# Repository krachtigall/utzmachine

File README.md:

# UTZmachine
A multi-user MIDI-controller and sampler.

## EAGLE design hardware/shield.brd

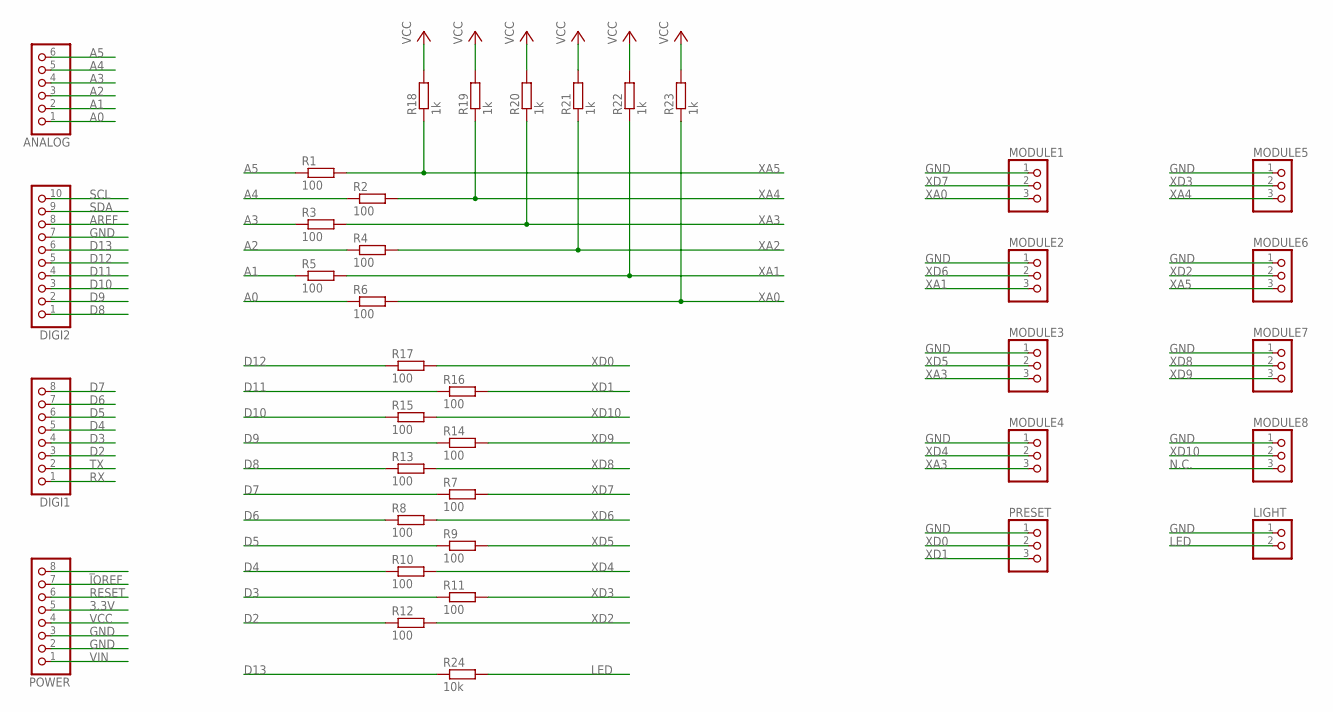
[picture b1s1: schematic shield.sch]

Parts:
ANALOG: PINHD-1X6; 1X06
DIGI1: PINHD-1X8; 1X08
DIGI2: PINHD-1X10; 1X10
LIGHT: PINHD-1X2; 1X02
MODULE1, MODULE2, MODULE3, MODULE4, MODULE5, MODULE6, MODULE7, MODULE8: PINHD-1X3; 1X03
POWER: PINHD-1X8; 1X08
PRESET: PINHD-1X3; 1X03
R1, R2, R3, R4, R5, R6, R7, R8, R9, R10, R11, R12, R13, R14, R15, R16, R17: 100; 0207/7
R18, R19, R20, R21, R22, R23: 1k; 0207/7
R24: 10k; 0207/7

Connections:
3.3V: POWER.5
A0: ANALOG.1, R6.1
A1: ANALOG.2, R5.1
A2: ANALOG.3, R4.1
A3: ANALOG.4, R3.1
A4: ANALOG.5, R2.1
A5: ANALOG.6, R1.1
AREF: DIGI2.8
D2: DIGI1.3, R12.1
D3: DIGI1.4, R11.1
D4: DIGI1.5, R10.1
D5: DIGI1.6, R9.1
D6: DIGI1.7, R8.1
D7: DIGI1.8, R7.1
D8: DIGI2.1, R13.1
D9: DIGI2.2, R14.1
D10: DIGI2.3, R15.1
D11: DIGI2.4, R16.1
D12: DIGI2.5, R17.1
D13: DIGI2.6, R24.1
GND: DIGI2.7, LIGHT.1, MODULE1.1, MODULE2.1, MODULE3.1, MODULE4.1, MODULE5.1, MODULE6.1, MODULE7.1, MODULE8.1, POWER.2, POWER.3, PRESET.1
IOREF: POWER.7
LED: LIGHT.2, R24.2
N.C.: MODULE8.3
RESET: POWER.6
RX: DIGI1.1
SCL: DIGI2.10
SDA: DIGI2.9
TX: DIGI1.2
VCC: POWER.4, R18.2, R19.2, R20.2, R21.2, R22.2, R23.2
VIN: POWER.1
XA0: MODULE1.3, R6.2, R23.1
XA1: MODULE2.3, R5.2, R22.1
XA2: R4.2, R21.1
XA3: MODULE3.3, MODULE4.3, R3.2, R20.1
XA4: MODULE5.3, R2.2, R19.1
XA5: MODULE6.3, R1.2, R18.1
XD0: PRESET.2, R17.2
XD1: PRESET.3, R16.2
XD2: MODULE6.2, R12.2
XD3: MODULE5.2, R11.2
XD4: MODULE4.2, R10.2
XD5: MODULE3.2, R9.2
XD6: MODULE2.2, R8.2
XD7: MODULE1.2, R7.2
XD8: MODULE7.2, R13.2
XD9: MODULE7.3, R14.2
XD10: MODULE8.2, R15.2
_: POWER.8

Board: 2 copper layers, 38 parts (0 on the bottom side), 38 nets, no tracks yet.

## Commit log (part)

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2014-08-24 Add sequencable harmonic oscillator
2014-08-25 added jimmmps matrixctrl
2014-08-25 add trigger-matrix to harmonic oscillator
2014-08-25 Removed matrix.pd as it was corrupt
2014-08-25 split gui_MetronomeBPM.pd to gui_metroBPM.pd & gui_metroClick.pd
2014-08-31 establish folder structure hierarchy
2014-08-31 gui elements get own folder
2014-08-31 add basic midi functions
2014-08-31 implement 4/8-track samplers with filedialog and preset saving
2014-08-31 clean up presets
2014-08-31 improve sampler gui and create single-channel mixer abstraction
2014-08-31 samplerX4: use just one bar for loading/saving samples
2014-08-31 increase size of sampler buttons
2014-08-31 remove filename dump from samplerX4
2014-09-01 change stopWatch behavior, rename gui-stopWatch to countDown and adapt modules that used those
2014-09-01 remove duplicate file stopWatchSec from utls
2014-09-01 implement tap metro with gui interface abstraction
2014-09-01 insert split object to prevent glitching metronome
2014-09-01 implement oneButtonTapMetro to loop kickdrum and by the way make the sampler midi-compatible
2014-09-02 autostart dsp on workspace
2014-10-04 add abstraction for mpkmini midi-input
2014-10-04 add record abstraction and guitar input abstraction for soundcard input
2014-10-04 add conversion abstraction ms -> bpm
2014-10-04 display peaks in mixer vu meters
2014-10-04 add preset choosing via midi pgmin
2014-10-04 remove dac~ from metroclick as outlet should be used
2014-10-04 create blue canvas for mixer
2014-10-04 midi-ctrlin -> volumes
2014-10-18 Make workspaceMPK ready for raspberry pi autostart
2014-10-18 create utz start script
2014-10-18 mv contents from workspaceMPK to utz
2014-10-18 create utz starters for pc and pi
2014-10-18 remove unused import from tapmetronome
2014-10-18 add multimelody composition as utz start theme
2014-10-18 dont output gui on top screen
2014-10-18 update starters for new utz name
2014-10-18 refactor mixer
2014-10-20 refactor sampler and add stop functionality to midi triggering
2014-10-20 implement mixer controller
2014-10-20 divide controls from audio processing in utz
2014-10-20 refine division
2014-10-20 remove gui from mixer
2014-10-20 add debug output for ctrlin and midiin
2014-10-20 remove usage of mpkmini
2014-10-20 remove mpkmini completely from patch
2014-10-20 remove controls subpatch
2014-10-20 use isolated mokdmini but dummy controls
2014-10-20 get original state without midisettings
2014-10-20 something wrong happened before...?
2014-10-20 initialize tapmetronome and increase shortest timedelta
2014-10-20 use ms instead of bpm to determine holdtime in tapmetro
2014-10-21 convert ms to sec in tapmetro
2014-10-21 add midi2multimelody starter
2014-10-21 include volume regulation
2014-10-21 fix volume bug: volume has to come before channel parameter
2014-10-21 initialize with program 0
2015-04-09 make it work for rpi2
2015-04-11 change samples
2015-04-11 change samples
    Former-commit-id: 6ad278d7dba5dec8e45f674af13e3b24edb2dd50
2015-04-11 change mixer preset
2015-04-11 change mixer preset
    Former-commit-id: fc8fc83804000022c28806eea7a8244acc8a80d2
2015-04-13 change folder hierarchy and add arduino code
2015-04-13 change folder hierarchy and add arduino code
    Former-commit-id: 4af9eda9a0f707cc4df91bc7a5c57a14eb1e80e2
2015-04-13 change title of readme
    Former-commit-id: 303448db32083d634248e22ad676e04bafbfdc8e
2015-04-13 change title of readme
2015-04-13 disable serial output in arduino, just midi
    Former-commit-id: dcb919f05f4d9623bf658745866063d46e17e54f
2015-04-13 disable serial output in arduino, just midi
2015-04-17 boot faster by disabling xserver and puredata gui
    Former-commit-id: 6f91886cbcc5b2535c9b803af497e224f4868a03
2015-04-17 ignore samples for git upload
    Former-commit-id: 174a87c80b387c9b076ec8fa7e3e67d1659b825e
2015-04-17 move samples&presets to dedicated folders and ignore samples for git-upload
    Former-commit-id: 113d126a3d72a1e5f85f512db10632a4e1838f71
2015-04-18 fix file permissions and write script for this
2015-05-09 add two midi-buttons
2015-05-09 implement preset switching on arduino and puredata
2015-05-09 write install script for raspberry
2015-05-09 use just one volume initialization in controls to prevent confusion
2015-05-09 add envelope to sample-player-abstraction
2015-05-09 decrease multiMelody volume
2015-05-09 change install scripts because ip/hostname is different for direct connection
2015-05-09 increase decay time for sample-playback
2015-05-11 write script for converting samples to 2-channel 44.1kHz wavs
2015-05-11 use line~ in sampler for better timing resolution
2015-09-22 sort samples and change presets
2015-09-22 create download script
2015-09-22 add gitignore file to omit uploading samples and downloaded files
2015-09-22 create script for packing samples and change way of gitignore to create download folder
2015-09-22 add remote way to start pd-application
2015-09-22 split audio subpatch in audio and master
2015-09-22 replace spigot by expression
2015-09-22 improve and tidy up main data-flow, refactor midi subpatch
2015-09-22 improve initialising
2015-09-22 remove automatic ending from multimelody and add instead stop meassage to init subpatch
2015-09-22 remove gui-controls from within sampler
2015-09-22 move preset handling from sampler to preset-subpatch
2015-09-23 working 8 samplers with loading presets and addressing
2015-09-23 change midi2msg conversion for new sampler
2015-09-23 small cosmetics
2015-09-24 add envelope settings to presets
2015-09-24 move preset switch to sampler-control UI and finetune envelope settings
2015-09-24 more envelope finetuning
2015-09-24 add volume values to presetloading
2015-09-25 randomPitchSocillator bugfix
2015-09-25 clean up some folders
2015-09-25 upload eagle files
2015-09-25 add poti connetions to schematic
2015-09-25 design schematic for one button and one poti
2015-09-25 add schematics for one and two button modules
2015-09-25 rename sampler to inst_sampler for clarity
2015-09-25 tidy up folders a bit more
2015-09-26 add ctrl2volume for mixing and set better levels
2015-09-26 add number box to preset switcher
2015-09-26 mix samples, now stage ready
2015-09-26 flatten µC folder
2015-09-26 first run of integrating kollabs library
2015-09-27 improve UI
2015-09-27 oops, sampler gui wasn't parametrized
2015-09-28 improve sampler GUI
2015-09-28 completely integrate kollabs for preset settings
2015-09-28 add midi adapter for kollabs scene change
2015-09-28 completely get rid of preset subpatch
2015-09-28 fix bug in midi_in: notein has misleading outlet order
2015-09-28 MIDI in is working with kollabs now
2015-09-28 midi notes -> samplers
2015-09-28 let sampler UI show start/stop-triggering
2015-09-28 change tapmetro to be kollabs-ready
2015-09-28 fix wrong midi_in parameters
2015-09-28 add adapter for mpkMini (receiving notes both on channel 1 and 10
2015-09-28 fall back to star pattern for audio flow
2015-09-29 create first draft of sampler based on array-reading
2015-09-29 preset folder isn't needed anymore, it's now all in preset.txt
2015-09-29 added pitch control to sampler
2015-09-29 added start/end-control to sampler
2015-09-29 add new sampler features to gui abstraction
2015-09-30 add midi consolue output for instant debuggin
2015-09-30 thought arduino sends midi on channel 1, but it's on 2
2015-09-30 get number of loaded presets
2015-10-02 new sampler is playing midi notes correctly
2015-10-02 add catch out to sampler
2015-10-02 use vline~ instead of phasor~ for sampler, as looping can't be set off easily. additionally this will allow more precise timing.
2015-10-04 found a way to use phasor and stop looping, even in reverse! this has to be integrated into the sampler now
2015-10-05 sampler tested, refactored, simplified
2015-10-05 add new features to sampler gui
2015-10-05 suppress sweeping noises from sampler
2015-10-05 add mute functionality to sampler
2015-10-05 replace old sampler with new sampler model. clicking is now present with some samples.
2015-10-05 remove debug print messages from sampler
2015-10-07 add rudimentary envelope to sampler. this poses new issues, as stopping array-playback happens simultanously to envelope-release which consequently renders the envelope uneffective. lots of clicks at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
2015-10-07 replace phasor with phasorshot to switch loop on/off in a way that is sample-accurate. Clicks are gone!
2015-10-07 add stoppable toggle to sampler gui
2015-10-07 small timing changes in sampler envelope
2015-10-07 loop/reverse/stoppable/left/right now in preset.txt
2015-10-08 add more basic midi deub output
2015-10-08 add miditest patch to test midi on a very low level
2015-10-08 start qjackctl before puredata to autoload midi devices
2015-10-08 autostart into lxde session and always start qjackctl with with utz. add all config files to new dedicated directory.
2015-10-08 use static ip: 192.168.2.155 to enable laptop configuration on the fly.
2015-10-08 wrong filename for patchbay. MIDI connection works on startup again!
2015-10-09 add script to print all logdata on screen
2015-10-11 add mkdmini to qjackctl patchbay
2015-10-14 prefix library in calling lib-objects in sampler
2015-12-09 add poti driving circuit to schematic and layout.
2015-12-09 flatten uC folder
2015-12-09 add support for potis on arduino
2015-12-09 small changes in schematic and layout
2015-12-21 add new potsounds preset.
2015-12-22 get sampler to work with deken libs
2015-12-22 disable relativepath..............
2015-12-22 midi control -> sampler pitch
2015-12-22 ooops... wrong midi notes.
2015-12-22 wron again -.-
2015-12-28 mpkmini -> volume control
2015-12-28 adjust scaling and offset for potis
2015-12-29 some working on this glitch bug. next thing will be refactoring, daisy chaining will be dropped, instead inlets will be reused again. this is puredata at last
2015-12-29 create dedicated volume abstraction
2015-12-29 create dedicated adsr abstraction (but not working yet!\)
2015-12-29 create module_sampler and help file for inst_sampler. lots of refactoring, next step is getting sampler back to work again.§
2015-12-29 parameter parsing and help file is working.
2015-12-30 added file-load-finished-outlet to sampler
2015-12-30 refactor file-loading subpatch
2015-12-30 refine fileloading.
2015-12-30 sampler is making noise again!
2015-12-30 sampler is working again completely \(at elast for first tests with complete help patch.\)
2015-12-30 enable realtime pitch again
2015-12-30 load file on trigger off
2015-12-30 add more kinds of modules
2015-12-30 fix looping bug.
2015-12-31 encapuslate play triggers in sampler. now this whole thing looks much simpler.
2015-12-31 prevent audio glitches on fileload.
2015-12-31 i should go to bed...
2015-12-31 fix fileloading bug.
2015-12-31 fix fileloading bug this time for real.
2015-12-31 last changes for this year...
2016-02-06 update ip in download script.
2016-02-25 add audio connections to patchbay
2016-02-25 get sampler back to work again! (I think...)
2016-03-22 Create new adsr-envelope-generator.
2016-04-09 working sampler module with adsr-envelope.
2016-04-09 remove unneeded env-new~
2016-04-09 create dummy modules for poti and repeater.
2016-04-09 working poti module.
2016-04-09 working repeater module. -> back to normal. :)
2016-04-09 small fixes for repeater module.
2016-04-09 two repeater modules! kick and snare!
2016-04-09 small documentation changes
2016-04-09 initial module_synth~ commit
2016-04-09 integrate synth module into utz dsp patch
2016-04-09 first working synth module!
2016-05-16 ommit using iemlib_prepend as I didn't manage to compile iemlib.
2016-05-16 change binary name to pd and add a gui start script.
2016-05-16 add some network changes as utzi had some dhcp/ip/etc problems. hope nobody minds i did this on this branch.
2016-05-17 remove global-mute setting from preset file.
2016-05-17 smoothen volume-envelope.
2016-05-17 quickly reload sample after depressing button to prevent audio glitches on preset changes on first sample start.
2016-05-17 improve triggering and fileloading in sampler further.
2016-05-17 last chance for a slow dance today...
